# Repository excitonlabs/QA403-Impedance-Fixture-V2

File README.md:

# QA403 Impedance Fixture V2

A test fixture for the QuantAsylum QA403 for measuring impedance based on Matt's blog posts:
* https://quantasylum.com/blogs/news/speaker-impedance-measurements
* https://quantasylum.com/blogs/news/measuring-input-impedance

This is version two of the text fixture and adds
 * optional attenuation before the inputs to the analyser
 * optional current sense resistor if you just want to use the board for connectivity.

The PCB is fairly flexible, there are three footprints for SMD currents sense resistors and a single through-hole footprint. These are in parallel so the expectation is you place one. The PCB also had an additional BNC for the L- input which may be useful for balanced measurements (BTL etc.).

## Using the attenuators

The analyser cannot have input voltages above 40V RMS, for use with high power amplifiers attenuation is needed. Three resistors form a T-pad before each input that can be used to preserve impedance if need. Alternatively, the T-pad can be reduced to a simple voltage divider by using a 0r resistor in the position before the coaxial socket.

### -6 dB attenuation using voltage divider

Place the following components to reduce the voltage the analysers measured by -6dBV:

* R5, R7, R9, R12 = 0r

* R6, R8, R10, R11, R13, R14, R15, R16 = 3k3

* All jumpers are open-circuit.

Voltage divider is a better option in general because it introduces less noise due to the lower resistances.

### -10dB attenuation using T-pad

Place the following components to reduce the voltage the analysers measured by -10dBV:

* R5, R6, R7, R8, R9, R10, R11, R12 = 52k

* R13, R14, R15, R16 = 72k

* All jumpers are open-circuit.

### Using the current sense

The right channel measures the voltage drop across the current sense resistor. Place an SMD resistor in any of the positions: R1, R2, R3, or R4. All of these are connected in parallel, so you can place more than one if you wish, just work out the resulting value. The smaller the resisor value the more noise will appear in the current measurement, the larger the resistor value the more it will load the circuit. Try and use a current sense 100 to 10 times smaller than the load.

### Disabling the attenuator

Do not place any resistors and short solder jumpers JP1, JP2, JP3, JP4.

### Disabling the current sense resistor

Short the solder jumper JP5.

## Questions

Forum post https://forum.quantasylum.com/t/comments-welcomed-on-test-fixture-pcb-for-impedance-measurements

## How to get this PCB

1. Order PCBs from a fab. house such as https://jlcpcb.com or email me, I have a few spare ones.
2. Order components from the BOM

## BOM

See datasheets in `/Parts` directory.

* Optional 2 x [MKDSN 1,5/ 2-5,08 1729128, terminal block](https://www.phoenixcontact.com/en-us/products/printed-circuit-board-terminal-mkdsn-15-2-508-1729128)
* Optional 2 x [Neutrik NMJ6HCD2, Jack socket](https://www.neutrik.com/en/product/nmj6hcd2)
* 4  x [TE Connectivity 5221123-2, BNC socket](https://www.te.com/usa-en/product-5221123-2.html)
* 1 x current sense resistor of the following types:
  * 2012 (5025)
  * 1206 (3216)
  * 0805 (2012)
  * Through-hole 

## Examples

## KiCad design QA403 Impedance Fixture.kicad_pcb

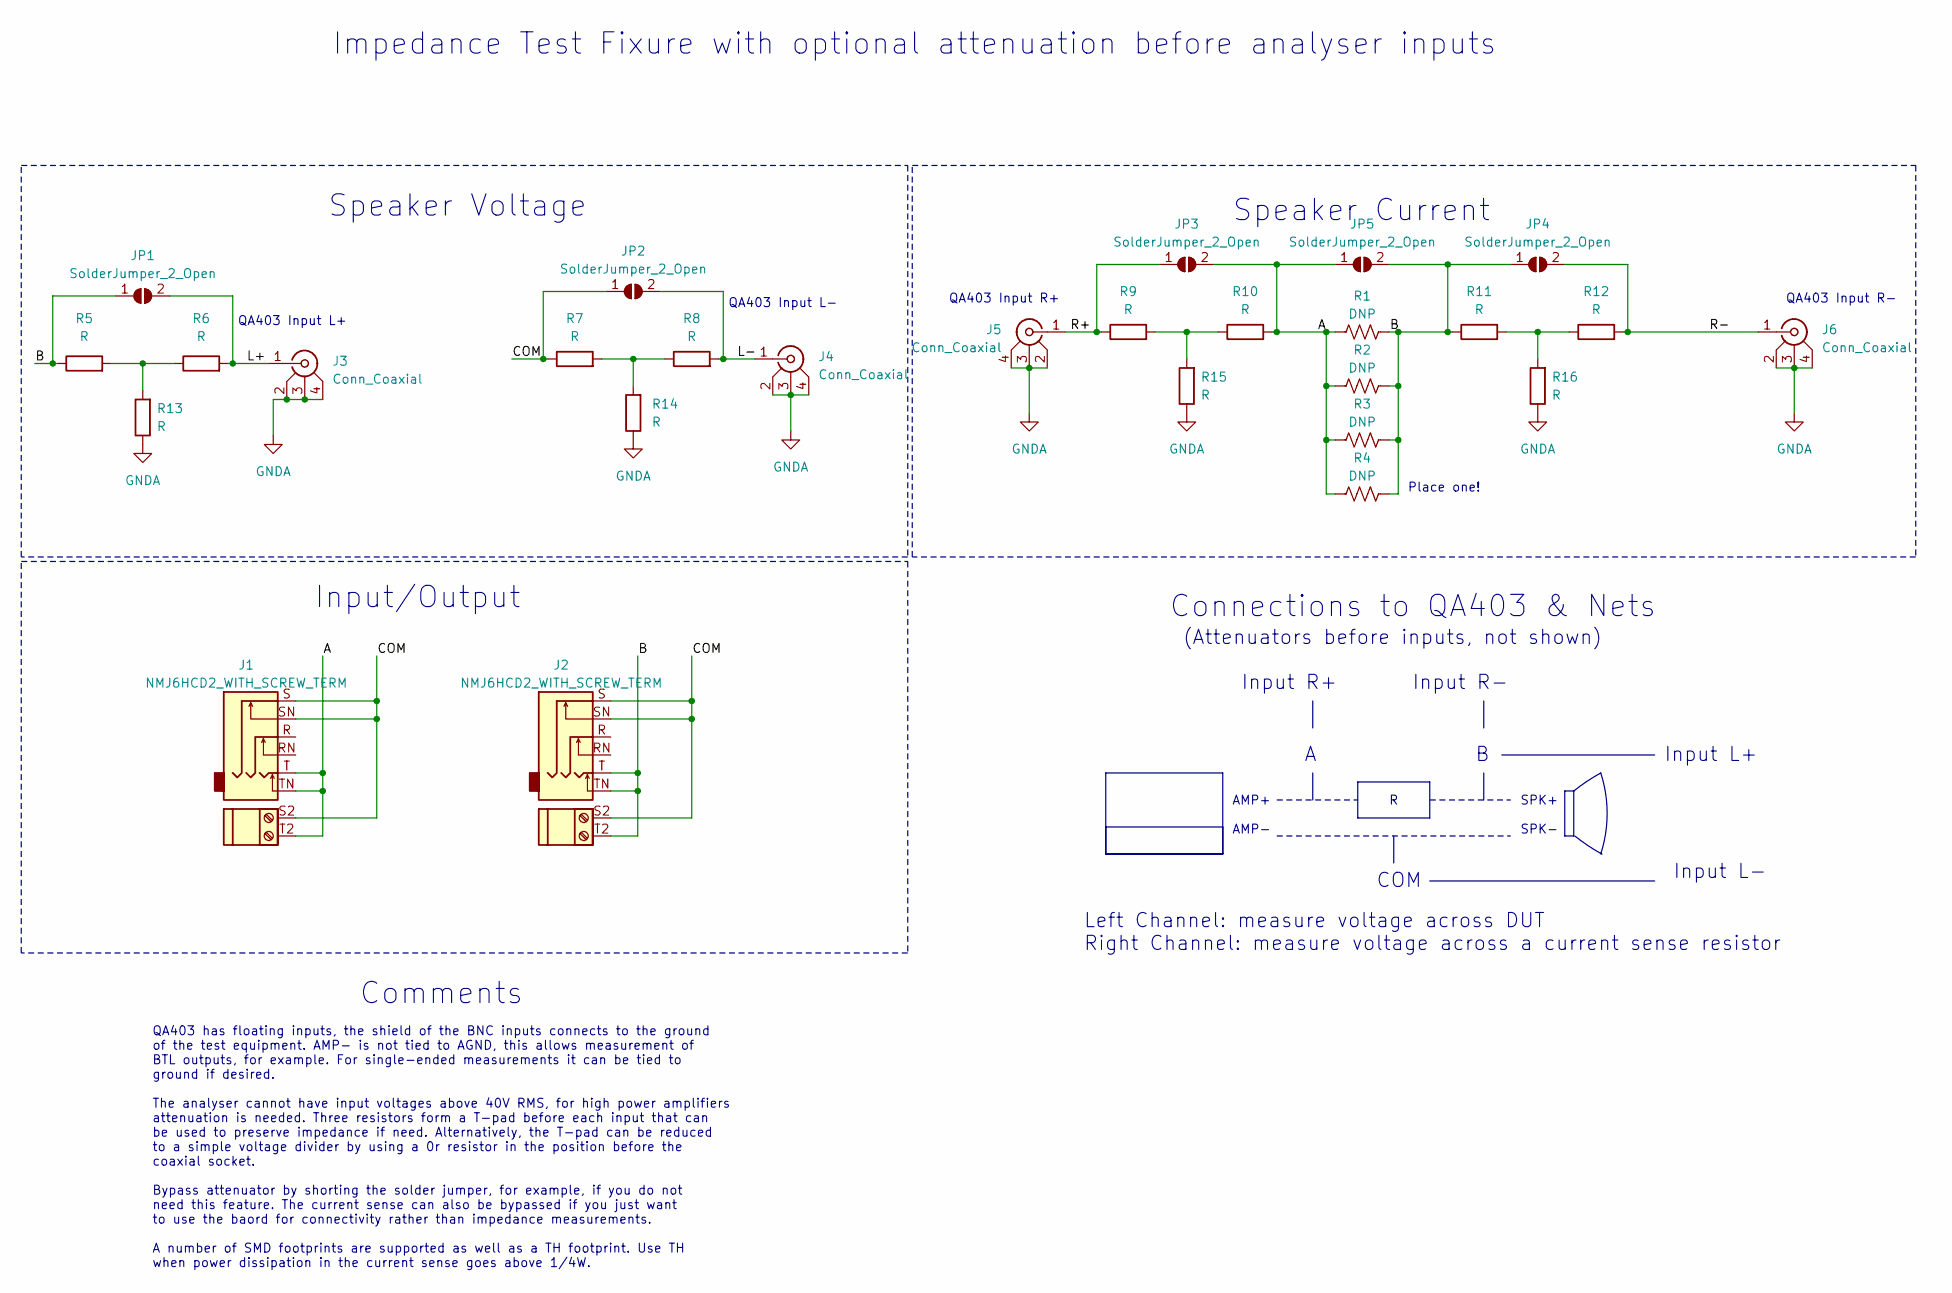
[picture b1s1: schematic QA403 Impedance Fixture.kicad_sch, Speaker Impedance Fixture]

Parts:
J1, J2: NMJ6HCD2_WITH_SCREW_TERM; Dual_Jack_6.35mm_Neutrik_NMJ6HCD2_Horizontal_TerminalBlock_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
J3, J4, J5, J6: Conn_Coaxial; 52211232
JP1, JP2, JP3, JP4, JP5: SolderJumper_2_Open; SolderJumper-2_P1.3mm_Open_TrianglePad1.0x1.5mm
R1: DNP; R_1206_3216Metric_Pad1.30x1.75mm_HandSolder
R2: DNP; R_0805_2012Metric_Pad1.20x1.40mm_HandSolder
R3: DNP; R_0603_1608Metric_Pad0.98x0.95mm_HandSolder
R4: DNP; R_SQM_20W_Resistor_45mm_20mm_12mm
R5, R6, R7, R8, R9, R10, R11, R12, R13, R14, R15, R16: R; R_1206_3216Metric

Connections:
/A: J1.T, J1.T2, J1.TN, JP3.2 (B), JP5.1 (A), R1.1, R2.1, R3.1, R4.1, R10.2
/B: J2.T, J2.T2, J2.TN, JP1.1 (A), JP4.1 (A), JP5.2 (B), R1.2, R2.2, R3.2, R4.2, R5.1, R11.1
/COM: J1.S, J1.S2, J1.SN, J2.S, J2.S2, J2.SN, JP2.1 (A), R7.1
/L+: J3.1 (In), JP1.2 (B), R6.2
/L-: J4.1 (In), JP2.2 (B), R8.2
/R+: J5.1 (In), JP3.1 (A), R9.1
/R-: J6.1 (In), JP4.2 (B), R12.2
GNDA: J3.2 (Ext), J3.3 (Ext), J3.4 (Ext), J4.2 (Ext), J4.3 (Ext), J4.4 (Ext), J5.2 (Ext), J5.3 (Ext), J5.4 (Ext), J6.2 (Ext), J6.3 (Ext), J6.4 (Ext), R13.1, R14.1, R15.1, R16.1
unnamed: R9.2, R10.1, R15.2
unnamed: R11.2, R12.1, R16.2
unnamed: R5.2, R6.1, R13.2
unnamed: R7.2, R8.1, R14.2

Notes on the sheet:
Speaker Current
Impedance Test Fixure with optional attenuation before analyser inputs
Speaker Voltage
QA403 Input R+
QA403 Input L+
(Attenuators before inputs, not shown)
Input L+
QA403 has floating inputs, the shield of the BNC inputs connects to the ground of the test equipment. AMP- is not tied to AGND, this allows measurement of BTL outputs, for example. For single-ended measurements it can be tied to ground if desired. The analyser cannot have input voltages above 40V R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
Input L-
Input/Output
AMP+ AMP-
Input R-
SPK+ SPK-
Comments
Input R+
QA403 Input R-
Left Channel: measure voltage across DUT Right Channel: measure voltage across a current sense resistor
QA403 Input L-
Connections to QA403 & Nets
COM
Place one!

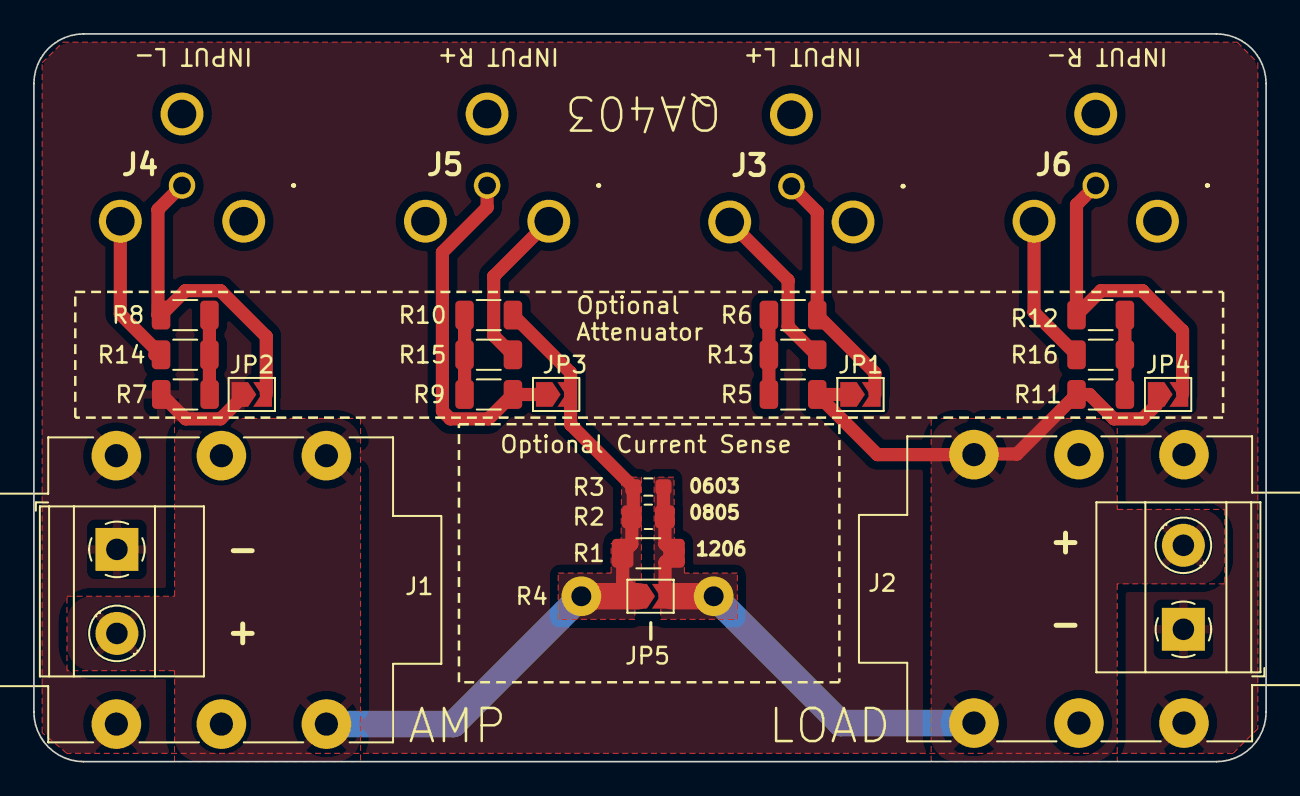
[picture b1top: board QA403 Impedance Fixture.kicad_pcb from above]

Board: 2 copper layers, 74.5 x 44.0 mm, 27 parts (0 on the bottom side), 12 nets.

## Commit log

2024-06-06 Add Images
2024-06-06 Add KiCad files
